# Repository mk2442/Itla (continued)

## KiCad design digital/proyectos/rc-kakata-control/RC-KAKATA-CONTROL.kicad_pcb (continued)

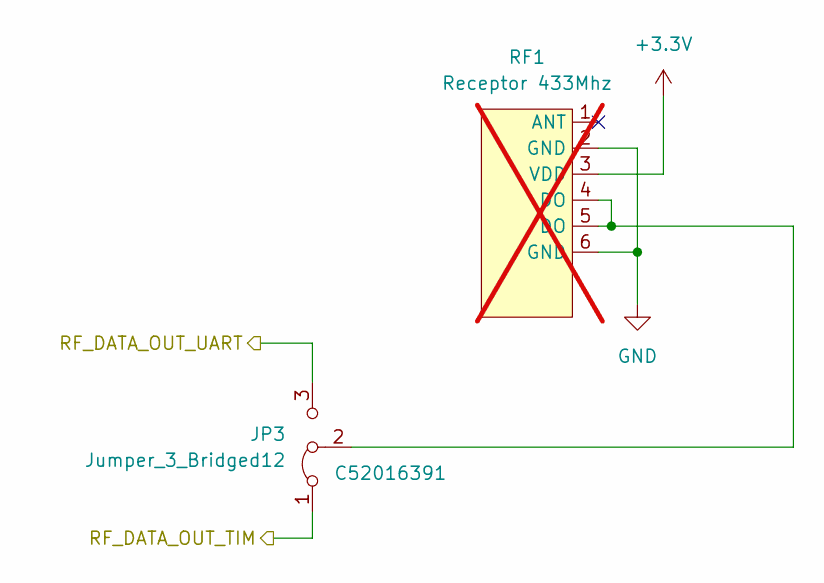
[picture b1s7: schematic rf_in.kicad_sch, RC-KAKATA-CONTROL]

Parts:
JP3: Jumper_3_Bridged12; PinHeader_1x03_P2.54mm_Vertical; LCSC Part C52016391
RF1: Receptor 433Mhz; rf_433mhz_receiver; not fitted

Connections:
+3.3V: RF1.3 (VDD); also elsewhere on the board
/RF_DATA_IN_TIM: JP3.1 (A); also elsewhere on the board
/RF_DATA_IN_UART: JP3.3 (B); also elsewhere on the board
GND: RF1.2 (GND), RF1.6 (GND); also elsewhere on the board
unnamed: JP3.2 (C), RF1.4 (DO), RF1.5 (DO)

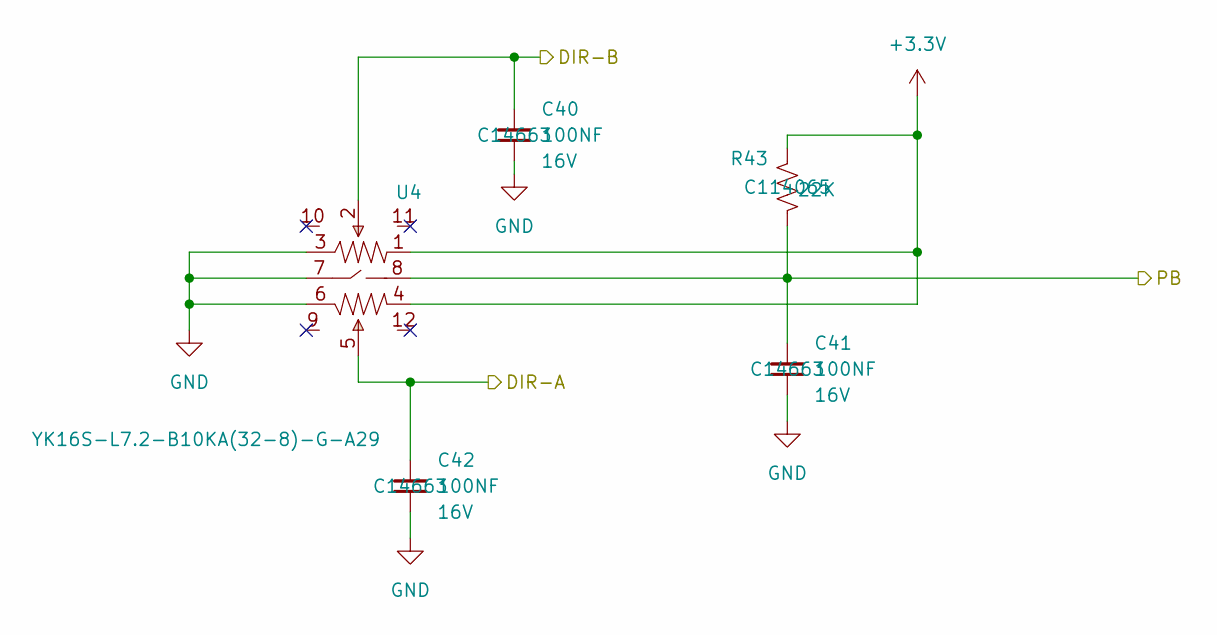
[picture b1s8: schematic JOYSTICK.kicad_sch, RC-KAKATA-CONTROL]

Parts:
C40, C41, C42: 100NF; C_0603; Part Number 0603YC104KAT2A; JLCPCB ID C14663
R43: 22K; R_0603; Part Number RC0603FR-0710KL; LCSC Part C114065
U4: YK16S-L7.2-B10KA(32-8)-G-A29; JOYTICK-TH_YF16S-FL7.2-B5KB-45-10-Y_1; LCSC Part C37323746

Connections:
+3.3V: R43.1, U4.1, U4.4; also elsewhere on the board
/JOY_DIRA: C42.2, U4.5; also elsewhere on the board
/JOY_DIRB: C41.2, R43.2, U4.8; also elsewhere on the board
/JOY_PB: C40.2, U4.2; also elsewhere on the board
GND: C40.1, C41.1, C42.1, U4.3, U4.6, U4.7; also elsewhere on the board

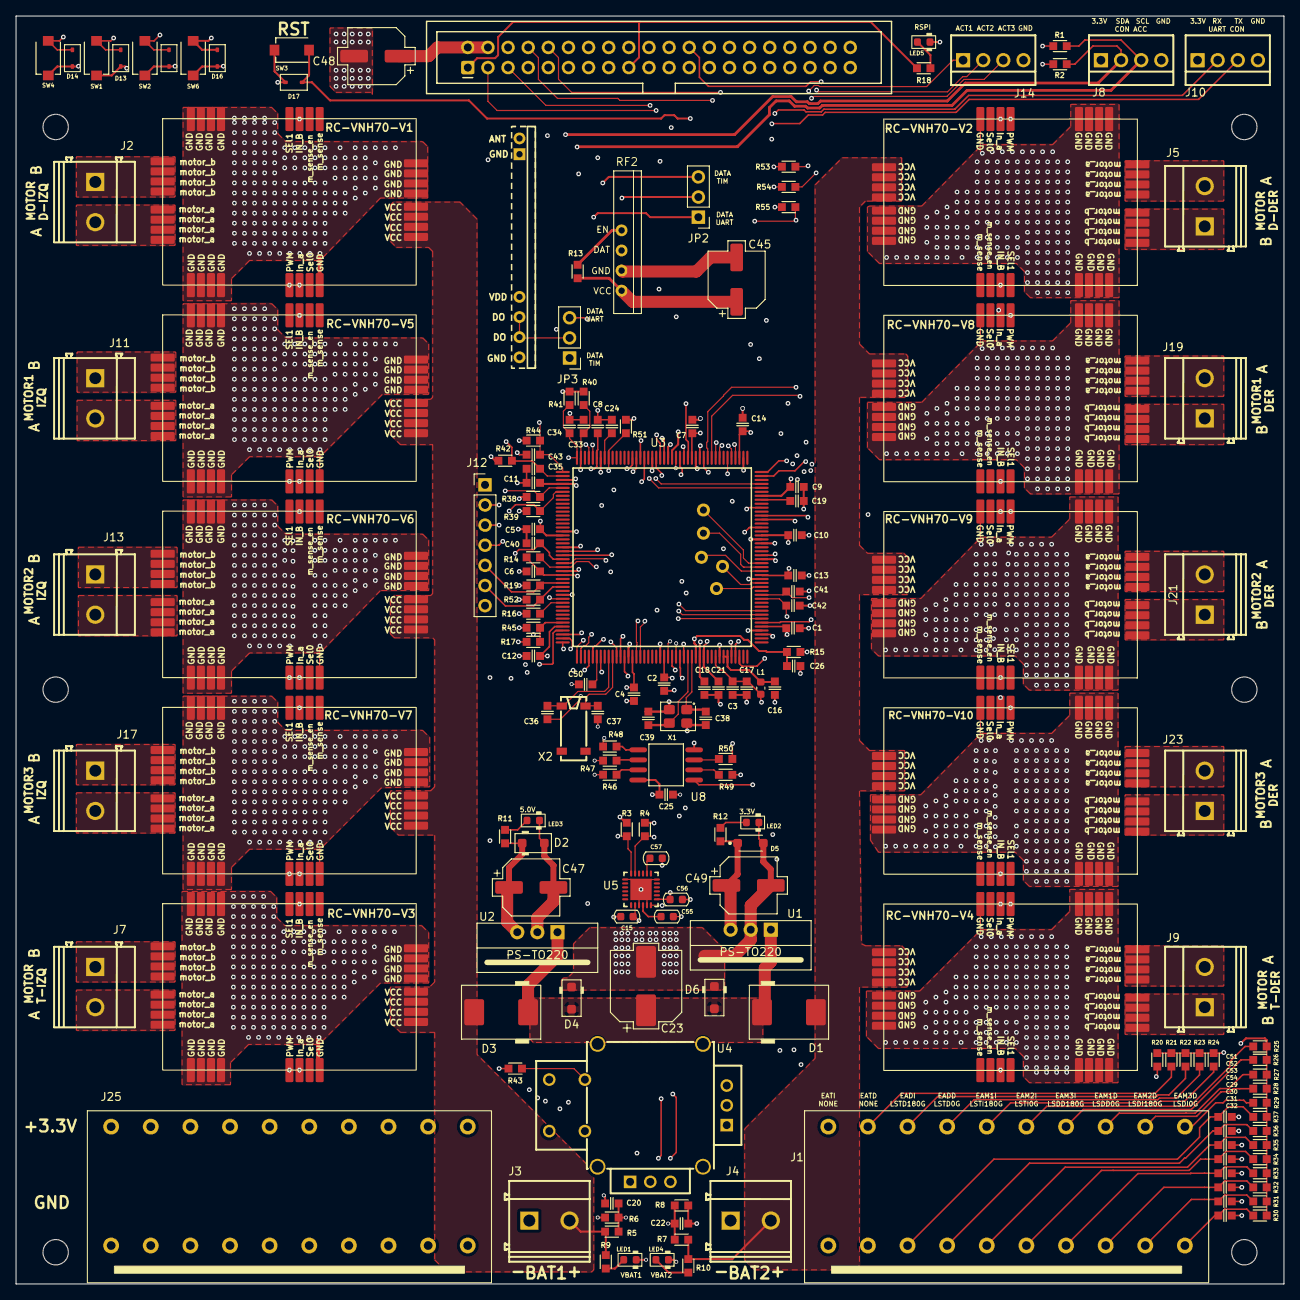
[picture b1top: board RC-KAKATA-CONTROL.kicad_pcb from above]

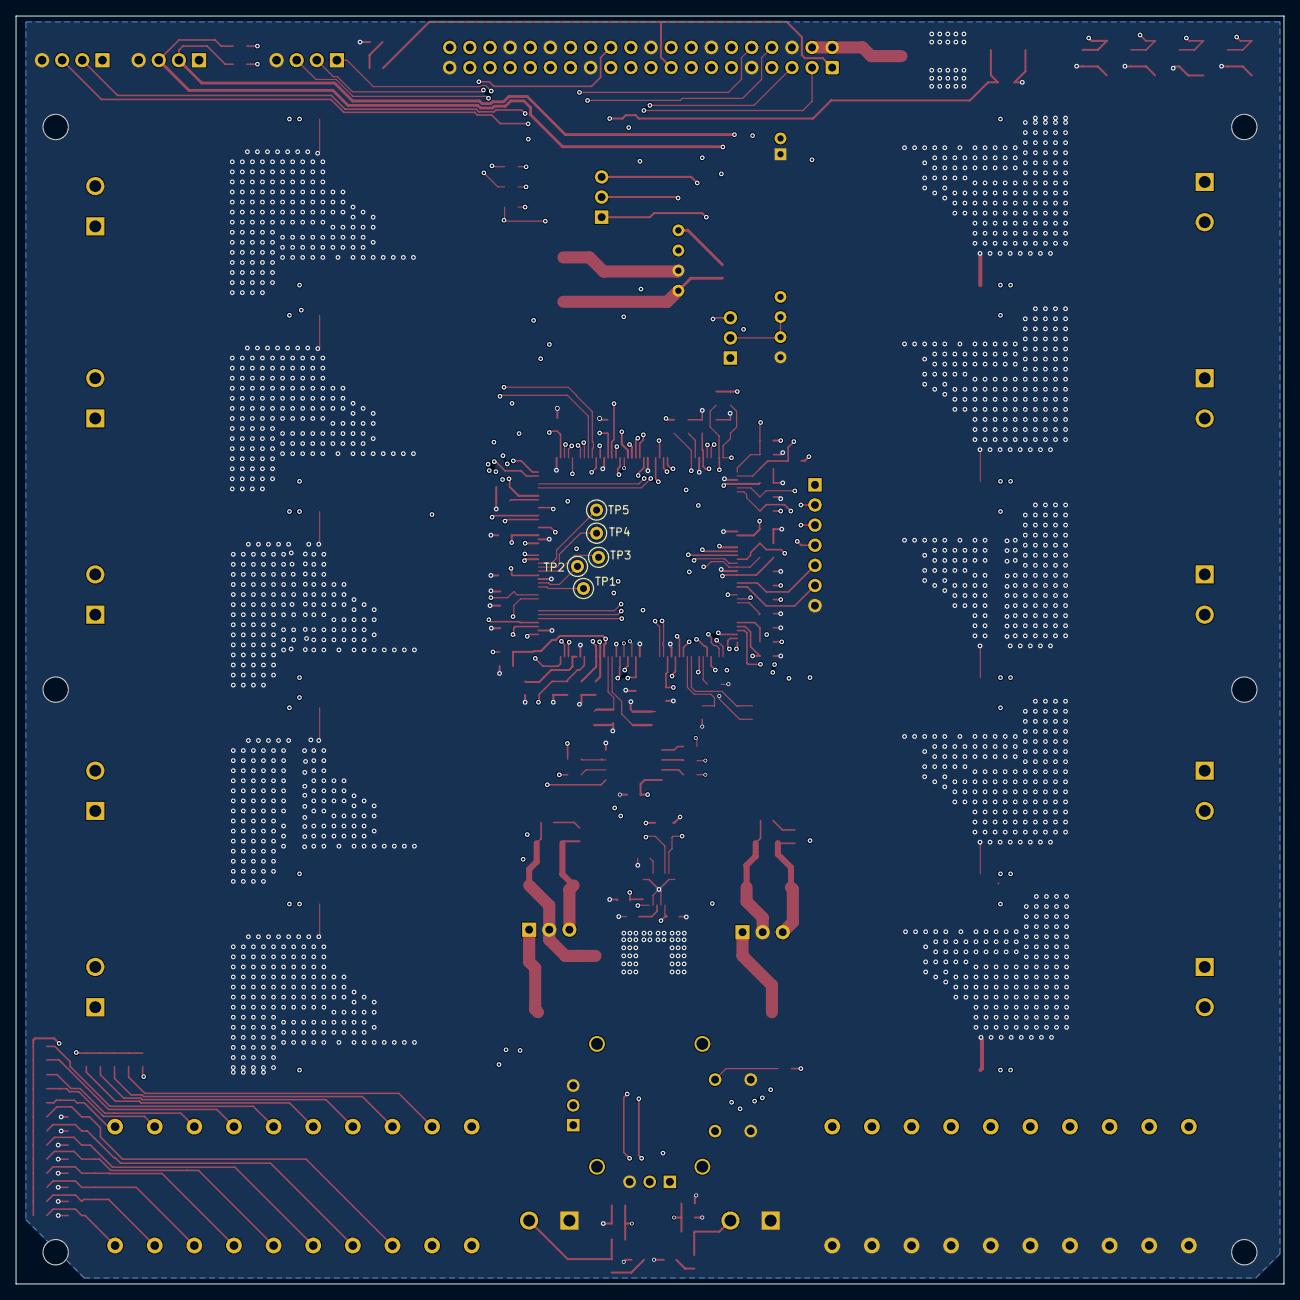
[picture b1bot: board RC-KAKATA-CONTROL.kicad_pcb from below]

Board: 6 copper layers, 160.0 x 160.0 mm, 182 parts (5 on the bottom side), 140 nets.

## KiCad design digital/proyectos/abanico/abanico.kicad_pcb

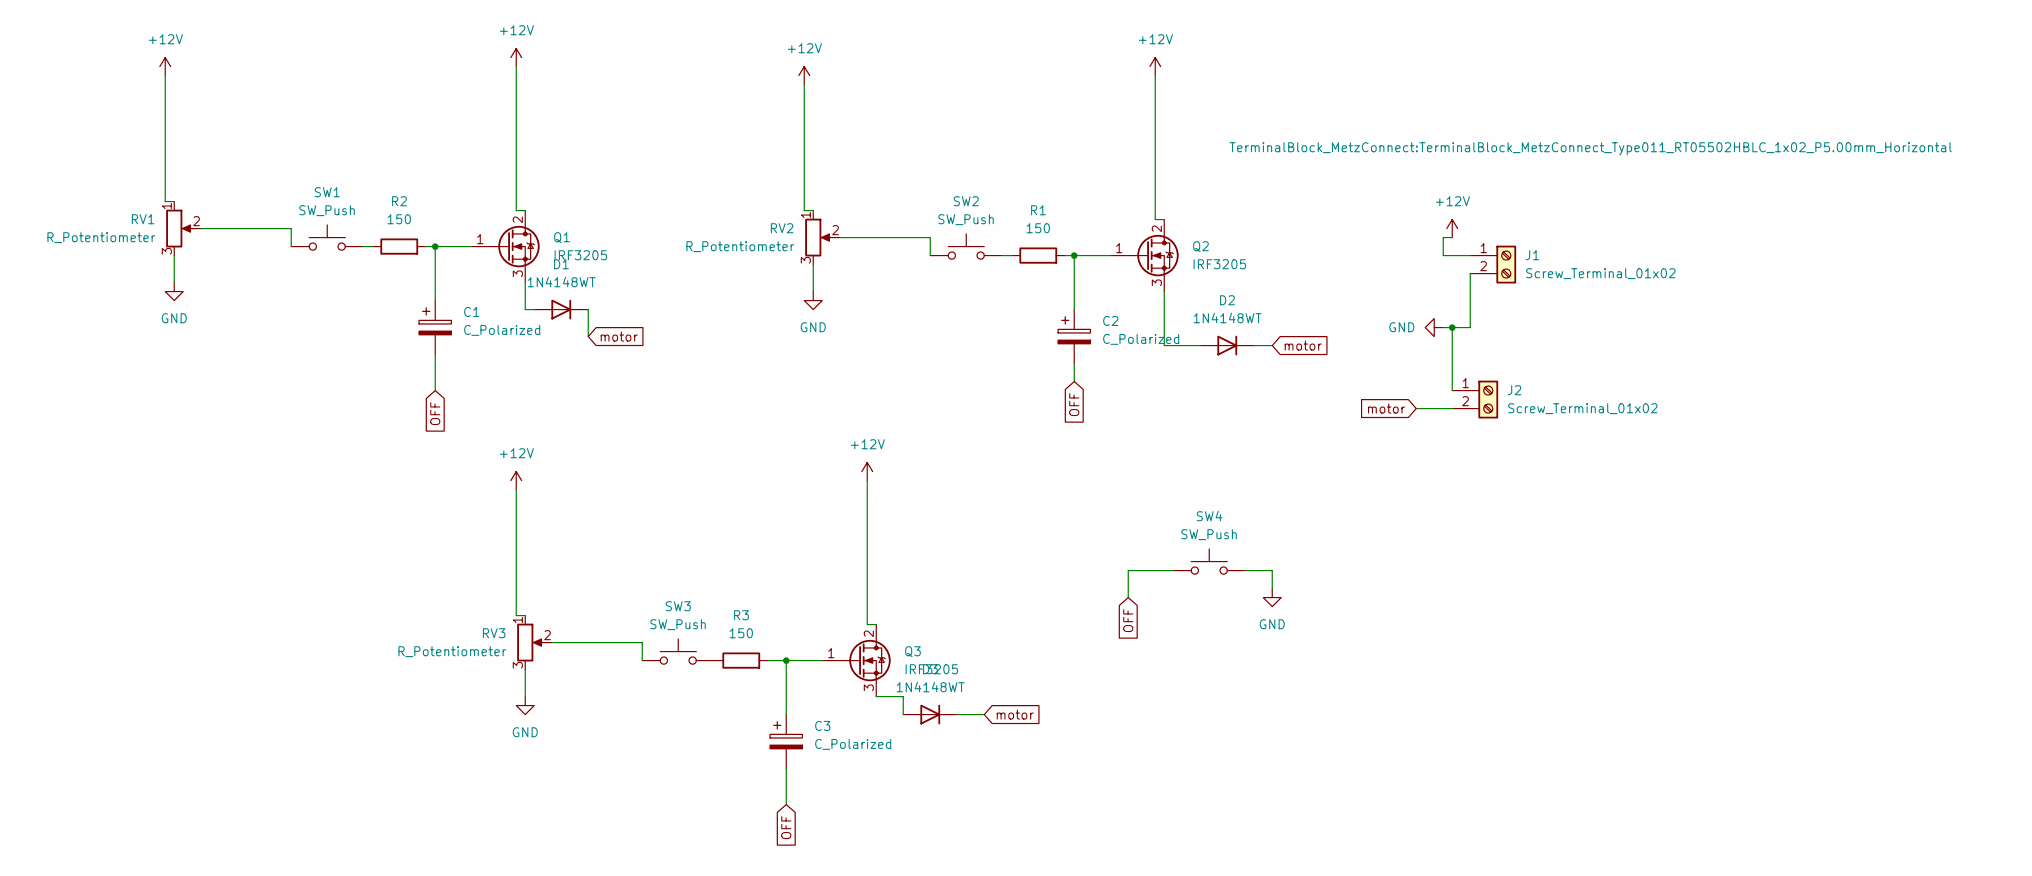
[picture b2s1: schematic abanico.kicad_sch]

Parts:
C1, C2, C3: C_Polarized; CP_Elec_3x5.3
D1, D2, D3: 1N4148WT; D_SOD-523
J1, J2: Screw_Terminal_01x02; TerminalBlock_MetzConnect_Type011_RT05502HBLC_1x02_P5.00mm_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
Q1, Q2, Q3: IRF3205; TO-220-3_Vertical
R1, R2, R3: 150; R_0201_0603Metric_Pad0.64x0.40mm_HandSolder
RV1, RV2, RV3: R_Potentiometer; Potentiometer_ACP_CA6-VSMD_Vertical
SW1, SW2, SW3, SW4: SW_Push; SW_Push_1P1T_NO_CK_KMR2

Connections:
+12V: J1.1, Q1.2 (D), Q2.2 (D), Q3.2 (D), RV1.1, RV2.1, RV3.1
GND: J1.2, J2.1, RV1.3, RV2.3, RV3.3, SW4.2
unnamed: D1.2 (A), Q1.3 (S)
unnamed: D2.2 (A), Q2.3 (S)
unnamed: D3.2 (A), Q3.3 (S)
unnamed: C1.1, Q1.1 (G), R2.2
unnamed: C2.1, Q2.1 (G), R1.2
unnamed: C3.1, Q3.1 (G), R3.2
unnamed: R1.1, SW2.2
unnamed: R2.1, SW1.2
unnamed: R3.1, SW3.2
unnamed: RV1.2, SW1.1
unnamed: RV2.2, SW2.1
unnamed: RV3.2, SW3.1
OFF: C1.2, C2.2, C3.2, SW4.1
motor: D1.1 (K), D2.1 (K), D3.1 (K), J2.2

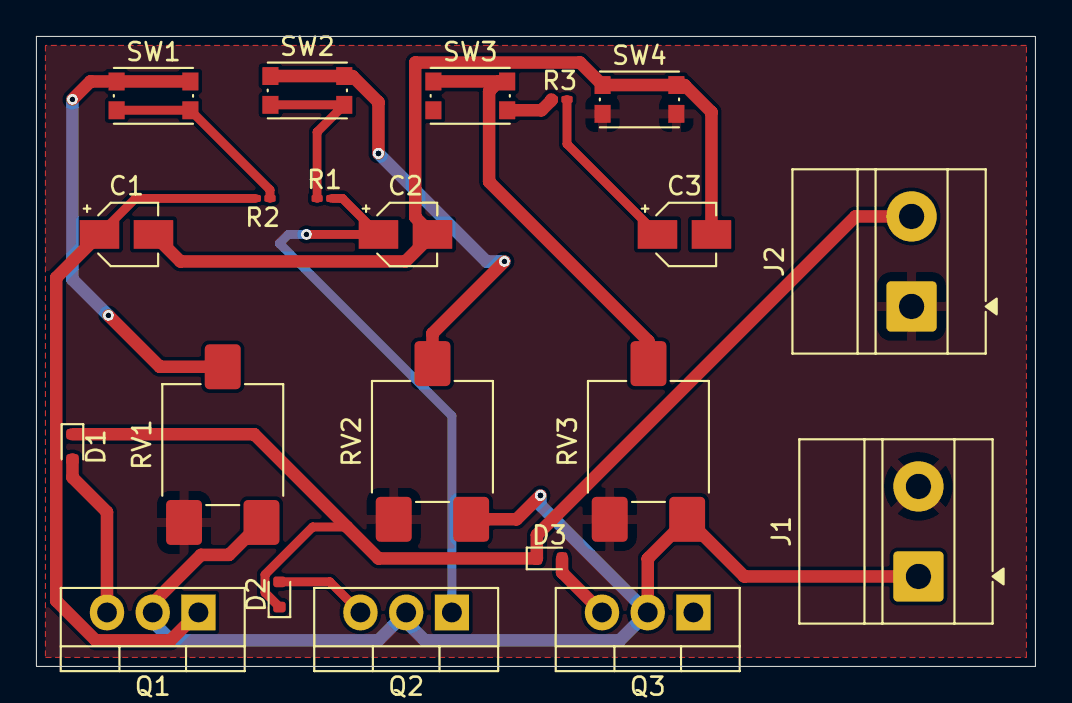
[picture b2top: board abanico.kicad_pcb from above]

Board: 2 copper layers, 55.5 x 35.0 mm, 21 parts (0 on the bottom side), 16 nets.

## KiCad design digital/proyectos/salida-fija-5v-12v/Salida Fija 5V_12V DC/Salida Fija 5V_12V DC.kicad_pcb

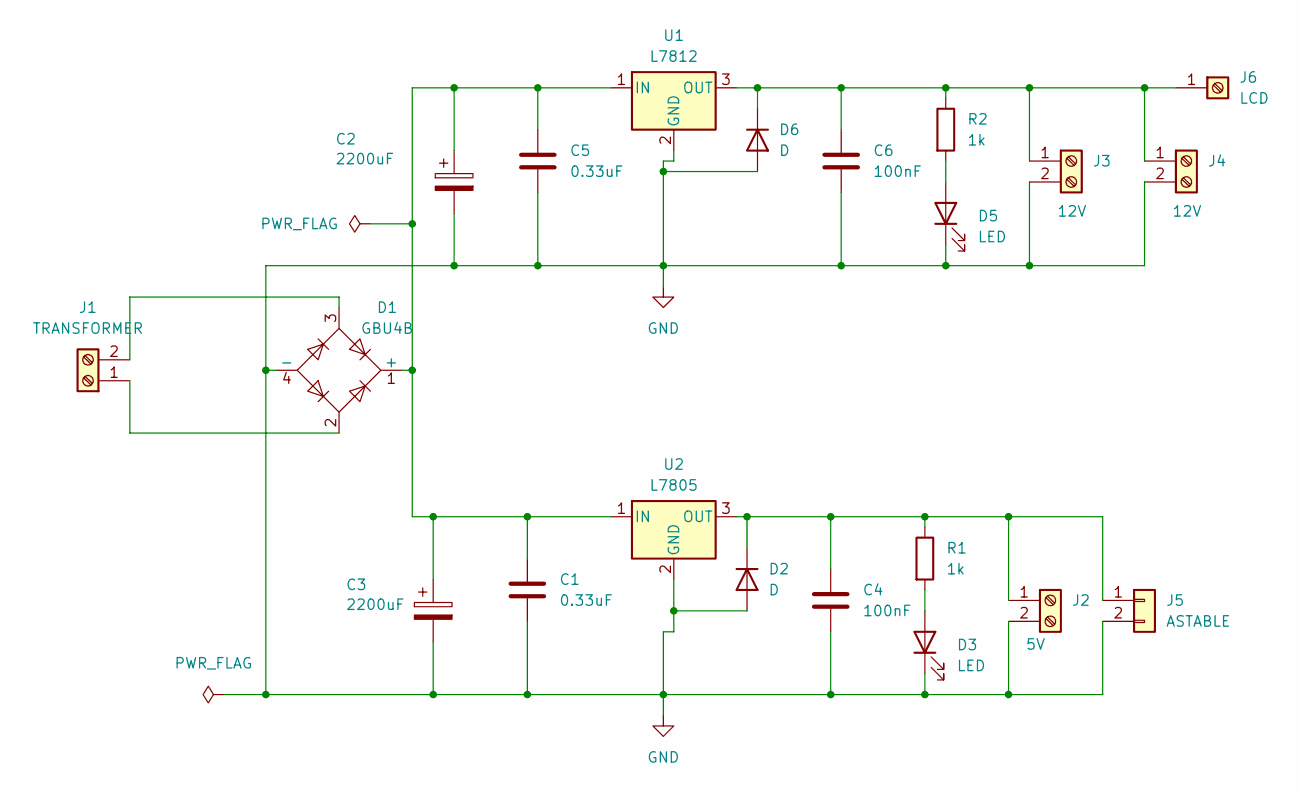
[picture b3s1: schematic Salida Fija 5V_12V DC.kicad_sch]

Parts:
C1, C5: 0.33uF; C_Disc_D5.0mm_W2.5mm_P5.00mm
C2, C3: 2200uF; CP_Radial_D12.5mm_P5.00mm
C4, C6: 100nF; C_Disc_D5.0mm_W2.5mm_P5.00mm
D1: GBU4B; Diode_Bridge_Vishay_GBU
D2, D6: D; D_DO-41_SOD81_P10.16mm_Horizontal
D3, D5: LED; LED_D5.0mm
J1: TRANSFORMER; TerminalBlock_Phoenix_MKDS-1,5-2_1x02_P5.00mm_Horizontal
J2: 5V; TerminalBlock_Phoenix_MKDS-1,5-2_1x02_P5.00mm_Horizontal
J3, J4: 12V; TerminalBlock_Phoenix_MKDS-1,5-2_1x02_P5.00mm_Horizontal
J5: ASTABLE; Molex_KK-254_AE-6410-02A_1x02_P2.54mm_Vertical
J6: LCD; TestPoint_THTPad_D2.5mm_Drill1.2mm
R1, R2: 1k; R_Axial_DIN0207_L6.3mm_D2.5mm_P10.16mm_Horizontal
U1: L7812; TO-220-3_Vertical
U2: L7805; TO-220-3_Vertical

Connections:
GND: C1.2, C2.2, C3.2, C4.2, C5.2, C6.2, D1.4 (-), D2.2 (A), D3.1 (K), D5.1 (K), D6.2 (A), J2.2, J3.2, J4.2, J5.2, U1.2 (GND), U2.2 (GND)
unnamed: C1.1, C2.1, C3.1, C5.1, D1.1 (+), U1.1 (IN), U2.1 (IN)
unnamed: C4.1, D2.1 (K), J2.1, J5.1, R1.1, U2.3 (OUT)
unnamed: D3.2 (A), R1.2
unnamed: D5.2 (A), R2.2
unnamed: C6.1, D6.1 (K), J3.1, J4.1, J6.1, R2.1, U1.3 (OUT)
unnamed: D1.2, J1.1
unnamed: D1.3, J1.2

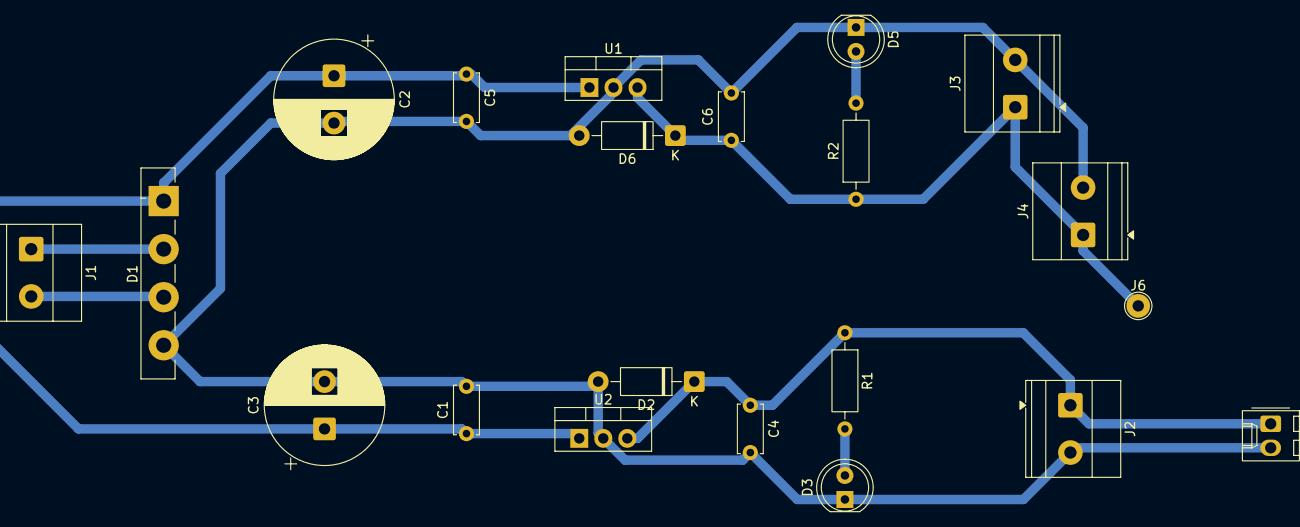
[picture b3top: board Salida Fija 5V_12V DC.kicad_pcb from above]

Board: 2 copper layers, 21 parts (0 on the bottom side), 8 nets.

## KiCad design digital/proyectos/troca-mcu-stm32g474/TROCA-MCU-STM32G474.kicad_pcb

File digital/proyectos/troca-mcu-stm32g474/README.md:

# TROCA-MCU-STM32G474
Tarjeta con microcontrolador STM32G474 100 pines, usamos PCB con pines gatillados.

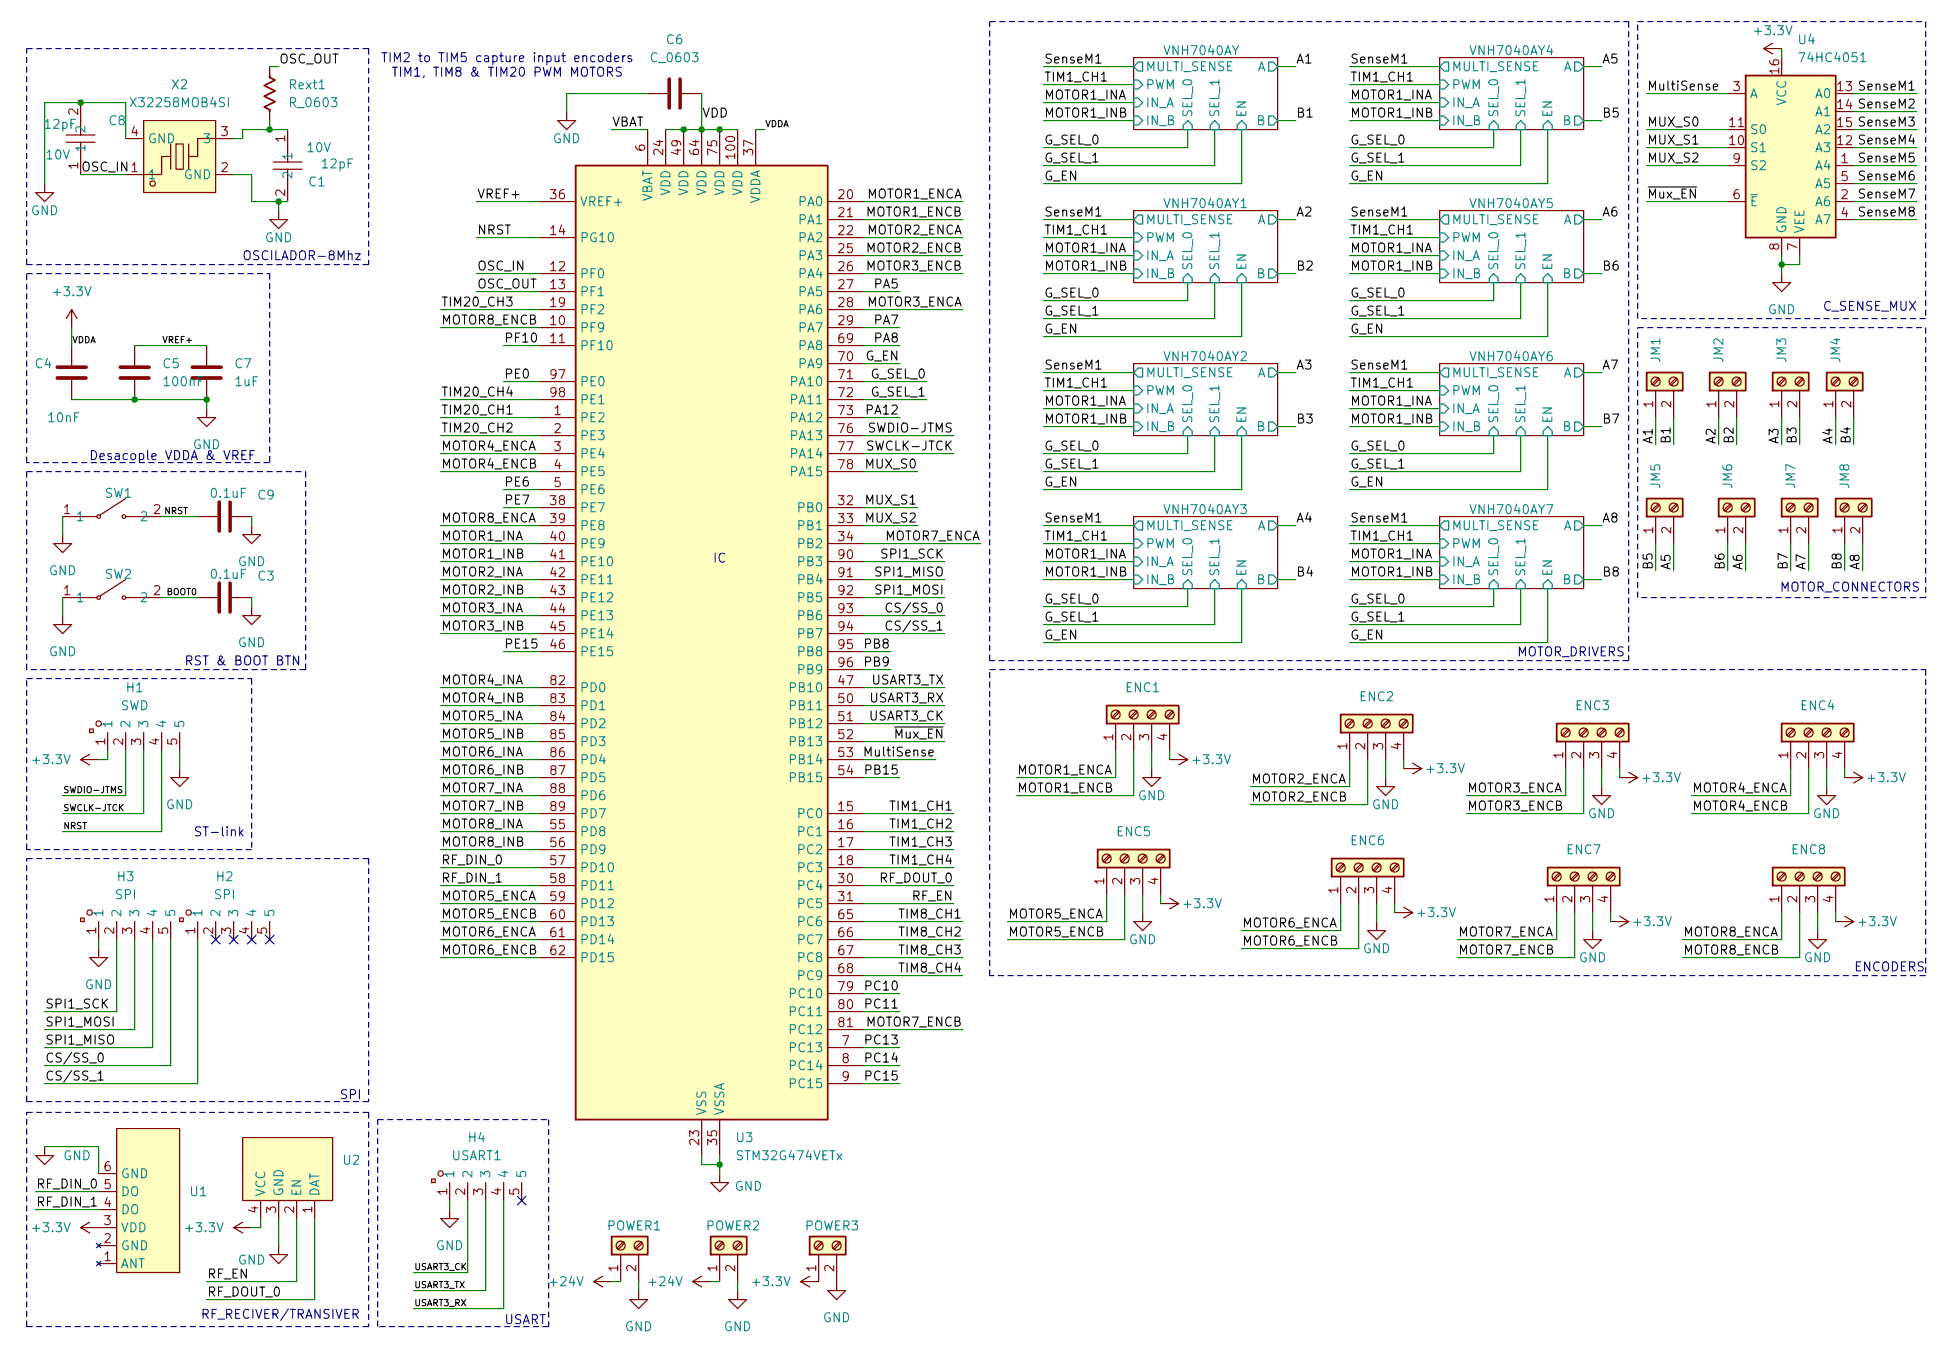
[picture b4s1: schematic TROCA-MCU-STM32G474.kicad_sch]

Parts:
C1, C8: 12pF; C0603; LCSC Part C2169734
C3, C9: 0.1uF; C_0603_1608Metric
C4: 10nF; C_0603_1608Metric
C5: 100nF; C_0603_1608Metric
C6: C_0603; C_0603_1608Metric
C7: 1uF; C_0603_1608Metric
ENC1, ENC2, ENC3, ENC4, ENC5, ENC6, ENC7, ENC8: Screw_Terminal_01x04; TerminalBlock_Xinya_XY308-2.54-4P_1x04_P2.54mm_Horizontal
H1: SWD; HDR-TH_5P-P2.00-V-M; LCSC Part C22438288
H2, H3: SPI; HDR-TH_5P-P2.00-V-M; LCSC Part C22438288
H4: USART1; HDR-TH_5P-P2.00-V-M; LCSC Part C22438288
JM1, JM2, JM3, JM4, JM5, JM6, JM7, JM8: Screw_Terminal_01x02; TerminalBlock_Xinya_XY308-2.54-2P_1x02_P2.54mm_Horizontal
POWER1, POWER2, POWER3: Screw_Terminal_01x02; TerminalBlock_Xinya_XY308-2.54-2P_1x02_P2.54mm_Horizontal
Rext1: R_0603; R_0603_1608Metric
SW1, SW2: HX-3X6X2.5-X SMD TACT SWITCH; SW-SMD_HX-3X6X2.5-X; LCSC Part C49234125
U1: rf_433mhz_receiver
U2: RF_433MHz_transmisor
U3: STM32G474VETx; LQFP-100_14x14mm_P0.5mm
U4: 74HC4051; PDIP-16_L19.3-W6.4-P2.54-LS7.94-BL
X2: X32258MOB4SI; CRYSTAL-SMD_4P-L3.2-W2.5-BL; LCSC Part C2682775

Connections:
+3.3V: C4.1, ENC1.4, ENC2.4, ENC3.4, ENC4.4, ENC5.4, ENC6.4, ENC7.4, ENC8.4, H1.1, POWER3.1, U1.3 (VDD), U2.4 (VCC), U3.37 (VDDA), U4.16 (VCC)
+24V: POWER1.1, POWER2.1; also elsewhere on the board
/A1: JM1.1; also elsewhere on the board
/A2: JM2.1; also elsewhere on the board
/A3: JM3.1; also elsewhere on the board
/A4: JM4.1; also elsewhere on the board
/A5: JM5.2; also elsewhere on the board
/A6: JM6.2; also elsewhere on the board
/A7: JM7.2; also elsewhere on the board
/A8: JM8.2; also elsewhere on the board
/B1: JM1.2; also elsewhere on the board
/B2: JM2.2; also elsewhere on the board
/B3: JM3.2; also elsewhere on the board
/B4: JM4.2; also elsewhere on the board
/B5: JM5.1; also elsewhere on the board
/B6: JM6.1; also elsewhere on the board
/B7: JM7.1; also elsewhere on the board
/B8: JM8.1; also elsewhere on the board
/BOOT0: C3.1, SW2.2
/CS/SS_0: H3.5, U3.93 (PB6)
/CS/SS_1: H2.1, U3.94 (PB7)
/G_EN: U3.70 (PA9); also elsewhere on the board
/G_SEL_0: U3.71 (PA10); also elsewhere on the board
/G_SEL_1: U3.72 (PA11); also elsewhere on the board
/MOTOR1_ENCA: ENC1.1, U3.20 (PA0)
/MOTOR1_ENCB: ENC1.2, U3.21 (PA1)
/MOTOR1_INA: U3.40 (PE9); also elsewhere on the board
/MOTOR1_INB: U3.41 (PE10); also elsewhere on the board
/MOTOR2_ENCA: ENC2.1, U3.22 (PA2)
/MOTOR2_ENCB: ENC2.2, U3.25 (PA3)
/MOTOR2_INA: U3.42 (PE11)
/MOTOR2_INB: U3.43 (PE12)
/MOTOR3_ENCA: ENC3.1, U3.28 (PA6)
/MOTOR3_ENCB: ENC3.2, U3.26 (PA4)
/MOTOR3_INA: U3.44 (PE13)
/MOTOR3_INB: U3.45 (PE14)
/MOTOR4_ENCA: ENC4.1, U3.3 (PE4)
/MOTOR4_ENCB: ENC4.2, U3.4 (PE5)
/MOTOR4_INA: U3.82 (PD0)
/MOTOR4_INB: U3.83 (PD1)
/MOTOR5_ENCA: ENC5.1, U3.59 (PD12)
/MOTOR5_ENCB: ENC5.2, U3.60 (PD13)
/MOTOR5_INA: U3.84 (PD2)
/MOTOR5_INB: U3.85 (PD3)
/MOTOR6_ENCA: ENC6.1, U3.61 (PD14)
/MOTOR6_ENCB: ENC6.2, U3.62 (PD15)
/MOTOR6_INA: U3.86 (PD4)
/MOTOR6_INB: U3.87 (PD5)
/MOTOR7_ENCA: ENC7.1, U3.34 (PB2)
/MOTOR7_ENCB: ENC7.2, U3.81 (PC12)
/MOTOR7_INA: U3.88 (PD6)
/MOTOR7_INB: U3.89 (PD7)
/MOTOR8_ENCA: ENC8.1, U3.39 (PE8)
/MOTOR8_ENCB: ENC8.2, U3.10 (PF9)
/MOTOR8_INA: U3.55 (PD8)
/MOTOR8_INB: U3.56 (PD9)
/MUX_S0: U3.78 (PA15), U4.11 (S0)
/MUX_S1: U3.32 (PB0), U4.10 (S1)
/MUX_S2: U3.33 (PB1), U4.9 (S2)
/MultiSense: U3.53 (PB14), U4.3 (A)
/NRST: C9.1, H1.4, SW1.2, U3.14 (PG10)
/OSC_IN: C8.1, U3.12 (PF0), X2.1
/OSC_OUT: Rext1.2, U3.13 (PF1)
/PA5: U3.27 (PA5)
/PA7: U3.29 (PA7)
/PA8: U3.69 (PA8)
/PA12: U3.73 (PA12)
/PB8: U3.95 (PB8)
/PB9: U3.96 (PB9)
/PB15: U3.54 (PB15)
/PC10: U3.79 (PC10)
/PC11: U3.80 (PC11)
/PC13: U3.7 (PC13)
/PC14: U3.8 (PC14)
/PC15: U3.9 (PC15)
/PE0: U3.97 (PE0)
/PE6: U3.5 (PE6)
/PE7: U3.38 (PE7)
/PE15: U3.46 (PE15)
/PF10: U3.11 (PF10)
/RF_DIN_0: U1.5 (DO), U3.57 (PD10)
/RF_DIN_1: U1.4 (DO), U3.58 (PD11)
/RF_DOUT_0: U2.1 (DAT), U3.30 (PC4)
/RF_EN: U2.2 (EN), U3.31 (PC5)
/SPI1_MISO: H3.4, U3.91 (PB4)
/SPI1_MOSI: H3.3, U3.92 (PB5)
/SPI1_SCK: H3.2, U3.90 (PB3)
/SWCLK-JTCK: H1.3, U3.77 (PA14)
/SWDIO-JTMS: H1.2, U3.76 (PA13)
/SenseM1: U4.13 (A0); also elsewhere on the board
/SenseM2: U4.14 (A1)
/SenseM3: U4.15 (A2)
/SenseM4: U4.12 (A3)
/SenseM5: U4.1 (A4)
/SenseM6: U4.5 (A5)
/SenseM7: U4.2 (A6)
/SenseM8: U4.4 (A7)
/TIM1_CH1: U3.15 (PC0); also elsewhere on the board
/TIM1_CH2: U3.16 (PC1)
/TIM1_CH3: U3.17 (PC2)
/TIM1_CH4: U3.18 (PC3)
/TIM8_CH1: U3.65 (PC6)
/TIM8_CH2: U3.66 (PC7)
/TIM8_CH3: U3.67 (PC8)
/TIM8_CH4: U3.68 (PC9)
/TIM20_CH1: U3.1 (PE2)
/TIM20_CH2: U3.2 (PE3)
/TIM20_CH3: U3.19 (PF2)
/TIM20_CH4: U3.98 (PE1)
/USART3_CK: H4.2, U3.51 (PB12)
/USART3_RX: H4.4, U3.50 (PB11)
/USART3_TX: H4.3, U3.47 (PB10)
/VBAT: U3.6 (VBAT)
/VDD: C6.1, U3.24 (VDD), U3.49 (VDD), U3.64 (VDD), U3.75 (VDD), U3.100 (VDD)
/VREF+: C5.1, C7.1, U3.36 (VREF+)
/~Mux_EN: U3.52 (PB13), U4.6 (~E)
GND: C1.2, C3.2, C4.2, C5.2, C6.2, C7.2, C8.2, C9.2, ENC1.3, ENC2.3, ENC3.3, ENC4.3, ENC5.3, ENC6.3, ENC7.3, ENC8.3, H1.5, H3.1, H4.1, POWER1.2, POWER2.2, POWER3.2, SW1.1, SW2.1, U1.6 (GND), U2.3 (GND), U3.23 (VSS), U3.35 (VSSA), U3.48 (VSS), U3.63 (VSS), U3.74 (VSS), U3.99 (VSS), U4.7 (VEE), U4.8 (GND), X2.2 (GND), X2.4 (GND); also elsewhere on the board
unnamed: C1.1, Rext1.1, X2.3

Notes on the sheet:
RF_RECIVER/TRANSIVER
TIM2 to TIM5 capture input encoders TIM1, TIM8 & TIM20 PWM MOTORS
OSCILADOR-8Mhz
MOTOR_CONNECTORS
MOTOR_DRIVERS
ENCODERS
Desacople VDDA & VREF
RST & BOOT BTN
C_SENSE_MUX
USART
SPI
ST-link

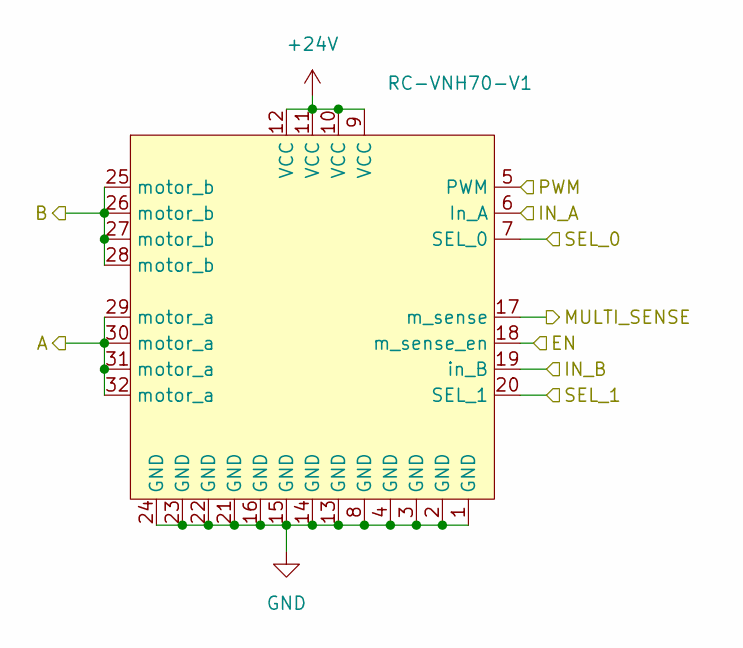
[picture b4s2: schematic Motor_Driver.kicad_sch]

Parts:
RC-VNH70-V1: RC-VNH70-V1

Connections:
+24V: RC-VNH70-V1.9 (VCC), RC-VNH70-V1.10 (VCC), RC-VNH70-V1.11 (VCC), RC-VNH70-V1.12 (VCC); also elsewhere on the board
/A1: RC-VNH70-V1.29 (motor_a), RC-VNH70-V1.30 (motor_a), RC-VNH70-V1.31 (motor_a), RC-VNH70-V1.32 (motor_a); also elsewhere on the board
/B1: RC-VNH70-V1.25 (motor_b), RC-VNH70-V1.26 (motor_b), RC-VNH70-V1.27 (motor_b), RC-VNH70-V1.28 (motor_b); also elsewhere on the board
/G_EN: RC-VNH70-V1.18 (m_sense_en); also elsewhere on the board
/G_SEL_0: RC-VNH70-V1.7 (SEL_0); also elsewhere on the board
/G_SEL_1: RC-VNH70-V1.20 (SEL_1); also elsewhere on the board
/MOTOR1_INA: RC-VNH70-V1.6 (In_A); also elsewhere on the board
/MOTOR1_INB: RC-VNH70-V1.19 (in_B); also elsewhere on the board
/SenseM1: RC-VNH70-V1.17 (m_sense); also elsewhere on the board
/TIM1_CH1: RC-VNH70-V1.5 (PWM); also elsewhere on the board
GND: RC-VNH70-V1.1 (GND), RC-VNH70-V1.2 (GND), RC-VNH70-V1.3 (GND), RC-VNH70-V1.4 (GND), RC-VNH70-V1.8 (GND), RC-VNH70-V1.13 (GND), RC-VNH70-V1.14 (GND), RC-VNH70-V1.15 (GND), RC-VNH70-V1.16 (GND), RC-VNH70-V1.21 (GND), RC-VNH70-V1.22 (GND), RC-VNH70-V1.23 (GND), RC-VNH70-V1.24 (GND); also elsewhere on the board

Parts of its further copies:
RC-VNH70-V2, RC-VNH70-V3, RC-VNH70-V4, RC-VNH70-V5, RC-VNH70-V6, RC-VNH70-V7, RC-VNH70-V8: RC-VNH70-V1

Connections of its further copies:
+24V: RC-VNH70-V2.9 (VCC), RC-VNH70-V2.10 (VCC), RC-VNH70-V2.11 (VCC), RC-VNH70-V2.12 (VCC), RC-VNH70-V3.9 (VCC), RC-VNH70-V3.10 (VCC), RC-VNH70-V3.11 (VCC), RC-VNH70-V3.12 (VCC), RC-VNH70-V4.9 (VCC), RC-VNH70-V4.10 (VCC), RC-VNH70-V4.11 (VCC), RC-VNH70-V4.12 (VCC), RC-VNH70-V5.9 (VCC), RC-VNH70-V5.10 (VCC), RC-VNH70-V5.11 (VCC), RC-VNH70-V5.12 (VCC), RC-VNH70-V6.9 (VCC), RC-VNH70-V6.10 (VCC), RC-VNH70-V6.11 (VCC), RC-VNH70-V6.12 (VCC), RC-VNH70-V7.9 (VCC), RC-VNH70-V7.10 (VCC), RC-VNH70-V7.11 (VCC), RC-VNH70-V7.12 (VCC), RC-VNH70-V8.9 (VCC), RC-VNH70-V8.10 (VCC), RC-VNH70-V8.11 (VCC), RC-VNH70-V8.12 (VCC); also elsewhere on the board
/A2: RC-VNH70-V2.29 (motor_a), RC-VNH70-V2.30 (motor_a), RC-VNH70-V2.31 (motor_a), RC-VNH70-V2.32 (motor_a); also elsewhere on the board
/A3: RC-VNH70-V3.29 (motor_a), RC-VNH70-V3.30 (motor_a), RC-VNH70-V3.31 (motor_a), RC-VNH70-V3.32 (motor_a); also elsewhere on the board
/A4: RC-VNH70-V4.29 (motor_a), RC-VNH70-V4.30 (motor_a), RC-VNH70-V4.31 (motor_a), RC-VNH70-V4.32 (motor_a); also elsewhere on the board
/A5: RC-VNH70-V5.29 (motor_a), RC-VNH70-V5.30 (motor_a), RC-VNH70-V5.31 (motor_a), RC-VNH70-V5.32 (motor_a); also elsewhere on the board
/A6: RC-VNH70-V6.29 (motor_a), RC-VNH70-V6.30 (motor_a), RC-VNH70-V6.31 (motor_a), RC-VNH70-V6.32 (motor_a); also elsewhere on the board
/A7: RC-VNH70-V7.29 (motor_a), RC-VNH70-V7.30 (motor_a), RC-VNH70-V7.31 (motor_a), RC-VNH70-V7.32 (motor_a); also elsewhere on the board
/A8: RC-VNH70-V8.29 (motor_a), RC-VNH70-V8.30 (motor_a), RC-VNH70-V8.31 (motor_a), RC-VNH70-V8.32 (motor_a); also elsewhere on the board
/B2: RC-VNH70-V2.25 (motor_b), RC-VNH70-V2.26 (motor_b), RC-VNH70-V2.27 (motor_b), RC-VNH70-V2.28 (motor_b); also elsewhere on the board
/B3: RC-VNH70-V3.25 (motor_b), RC-VNH70-V3.26 (motor_b), RC-VNH70-V3.27 (motor_b), RC-VNH70-V3.28 (motor_b); also elsewhere on the board
/B4: RC-VNH70-V4.25 (motor_b), RC-VNH70-V4.26 (motor_b), RC-VNH70-V4.27 (motor_b), RC-VNH70-V4.28 (motor_b); also elsewhere on the board
/B5: RC-VNH70-V5.25 (motor_b), RC-VNH70-V5.26 (motor_b), RC-VNH70-V5.27 (motor_b), RC-VNH70-V5.28 (motor_b); also elsewhere on the board
/B6: RC-VNH70-V6.25 (motor_b), RC-VNH70-V6.26 (motor_b), RC-VNH70-V6.27 (motor_b), RC-VNH70-V6.28 (motor_b); also elsewhere on the board
/B7: RC-VNH70-V7.25 (motor_b), RC-VNH70-V7.26 (motor_b), RC-VNH70-V7.27 (motor_b), RC-VNH70-V7.28 (motor_b); also elsewhere on the board
/B8: RC-VNH70-V8.25 (motor_b), RC-VNH70-V8.26 (motor_b), RC-VNH70-V8.27 (motor_b), RC-VNH70-V8.28 (motor_b); also elsewhere on the board
/G_EN: RC-VNH70-V2.18 (m_sense_en), RC-VNH70-V3.18 (m_sense_en), RC-VNH70-V4.18 (m_sense_en), RC-VNH70-V5.18 (m_sense_en), RC-VNH70-V6.18 (m_sense_en), RC-VNH70-V7.18 (m_sense_en), RC-VNH70-V8.18 (m_sense_en); also elsewhere on the board
/G_SEL_0: RC-VNH70-V2.7 (SEL_0), RC-VNH70-V3.7 (SEL_0), RC-VNH70-V4.7 (SEL_0), RC-VNH70-V5.7 (SEL_0), RC-VNH70-V6.7 (SEL_0), RC-VNH70-V7.7 (SEL_0), RC-VNH70-V8.7 (SEL_0); also elsewhere on the board
/G_SEL_1: RC-VNH70-V2.20 (SEL_1), RC-VNH70-V3.20 (SEL_1), RC-VNH70-V4.20 (SEL_1), RC-VNH70-V5.20 (SEL_1), RC-VNH70-V6.20 (SEL_1), RC-VNH70-V7.20 (SEL_1), RC-VNH70-V8.20 (SEL_1); also elsewhere on the board
/MOTOR1_INA: RC-VNH70-V2.6 (In_A), RC-VNH70-V3.6 (In_A), RC-VNH70-V4.6 (In_A), RC-VNH70-V5.6 (In_A), RC-VNH70-V6.6 (In_A), RC-VNH70-V7.6 (In_A), RC-VNH70-V8.6 (In_A); also elsewhere on the board
/MOTOR1_INB: RC-VNH70-V2.19 (in_B), RC-VNH70-V3.19 (in_B), RC-VNH70-V4.19 (in_B), RC-VNH70-V5.19 (in_B), RC-VNH70-V6.19 (in_B), RC-VNH70-V7.19 (in_B), RC-VNH70-V8.19 (in_B); also elsewhere on the board
/SenseM1: RC-VNH70-V2.17 (m_sense), RC-VNH70-V3.17 (m_sense), RC-VNH70-V4.17 (m_sense), RC-VNH70-V5.17 (m_sense), RC-VNH70-V6.17 (m_sense), RC-VNH70-V7.17 (m_sense), RC-VNH70-V8.17 (m_sense); also elsewhere on the board
/TIM1_CH1: RC-VNH70-V2.5 (PWM), RC-VNH70-V3.5 (PWM), RC-VNH70-V4.5 (PWM), RC-VNH70-V5.5 (PWM), RC-VNH70-V6.5 (PWM), RC-VNH70-V7.5 (PWM), RC-VNH70-V8.5 (PWM); also elsewhere on the board
GND: RC-VNH70-V2.1 (GND), RC-VNH70-V2.2 (GND), RC-VNH70-V2.3 (GND), RC-VNH70-V2.4 (GND), RC-VNH70-V2.8 (GND), RC-VNH70-V2.13 (GND), RC-VNH70-V2.14 (GND), RC-VNH70-V2.15 (GND), RC-VNH70-V2.16 (GND), RC-VNH70-V2.21 (GND), RC-VNH70-V2.22 (GND), RC-VNH70-V2.23 (GND), RC-VNH70-V2.24 (GND), RC-VNH70-V3.1 (GND), RC-VNH70-V3.2 (GND), RC-VNH70-V3.3 (GND), RC-VNH70-V3.4 (GND), RC-VNH70-V3.8 (GND), RC-VNH70-V3.13 (GND), RC-VNH70-V3.14 (GND), RC-VNH70-V3.15 (GND), RC-VNH70-V3.16 (GND), RC-VNH70-V3.21 (GND), RC-VNH70-V3.22 (GND), RC-VNH70-V3.23 (GND), RC-VNH70-V3.24 (GND), RC-VNH70-V4.1 (GND), RC-VNH70-V4.2 (GND), RC-VNH70-V4.3 (GND), RC-VNH70-V4.4 (GND), RC-VNH70-V4.8 (GND), RC-VNH70-V4.13 (GND), RC-VNH70-V4.14 (GND), RC-VNH70-V4.15 (GND), RC-VNH70-V4.16 (GND), RC-VNH70-V4.21 (GND), RC-VNH70-V4.22 (GND), RC-VNH70-V4.23 (GND), RC-VNH70-V4.24 (GND), RC-VNH70-V5.1 (GND), RC-VNH70-V5.2 (GND), RC-VNH70-V5.3 (GND), RC-VNH70-V5.4 (GND), RC-VNH70-V5.8 (GND), RC-VNH70-V5.13 (GND), RC-VNH70-V5.14 (GND), RC-VNH70-V5.15 (GND), RC-VNH70-V5.16 (GND), RC-VNH70-V5.21 (GND), RC-VNH70-V5.22 (GND), RC-VNH70-V5.23 (GND), RC-VNH70-V5.24 (GND), RC-VNH70-V6.1 (GND), RC-VNH70-V6.2 (GND), RC-VNH70-V6.3 (GND), RC-VNH70-V6.4 (GND), RC-VNH70-V6.8 (GND), RC-VNH70-V6.13 (GND), RC-VNH70-V6.14 (GND), RC-VNH70-V6.15 (GND), RC-VNH70-V6.16 (GND), RC-VNH70-V6.21 (GND), RC-VNH70-V6.22 (GND), RC-VNH70-V6.23 (GND), RC-VNH70-V6.24 (GND), RC-VNH70-V7.1 (GND), RC-VNH70-V7.2 (GND), RC-VNH70-V7.3 (GND), RC-VNH70-V7.4 (GND), RC-VNH70-V7.8 (GND), RC-VNH70-V7.13 (GND), RC-VNH70-V7.14 (GND), RC-VNH70-V7.15 (GND), RC-VNH70-V7.16 (GND), RC-VNH70-V7.21 (GND), RC-VNH70-V7.22 (GND), RC-VNH70-V7.23 (GND), RC-VNH70-V7.24 (GND), RC-VNH70-V8.1 (GND), RC-VNH70-V8.2 (GND), RC-VNH70-V8.3 (GND), RC-VNH70-V8.4 (GND), RC-VNH70-V8.8 (GND), RC-VNH70-V8.13 (GND), RC-VNH70-V8.14 (GND), RC-VNH70-V8.15 (GND), RC-VNH70-V8.16 (GND), RC-VNH70-V8.21 (GND), RC-VNH70-V8.22 (GND), RC-VNH70-V8.23 (GND), RC-VNH70-V8.24 (GND); also elsewhere on the board

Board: 4 copper layers, 47 parts (0 on the bottom side), 68 nets, no tracks yet.
